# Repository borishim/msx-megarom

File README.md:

# msx-megarom
MSX megarom cartridge pcb (kicad)

There are three jumpers to set:
- P8: put a jumper for 8kB bank, otherwise 16kB
- P7 and P2: bank selection bits (WA and WB). Depends on the mapper type.

For example,
```
                           8kB WA  WB
                     ASC8: YES A11 A12
                    ASC16: NO  A12 0
                 Generic8: YES A13 A15
                Generic16: NO  A15 0
               Konami SCC: YES A13 A15
            Konami no SCC: YES A13 A15
Super Game World 30/64/80: YES A0  A1
            Super Pierrot: NO  A12 0
```
Also take a look https://www.msx.org/wiki/MegaROM_Mappers

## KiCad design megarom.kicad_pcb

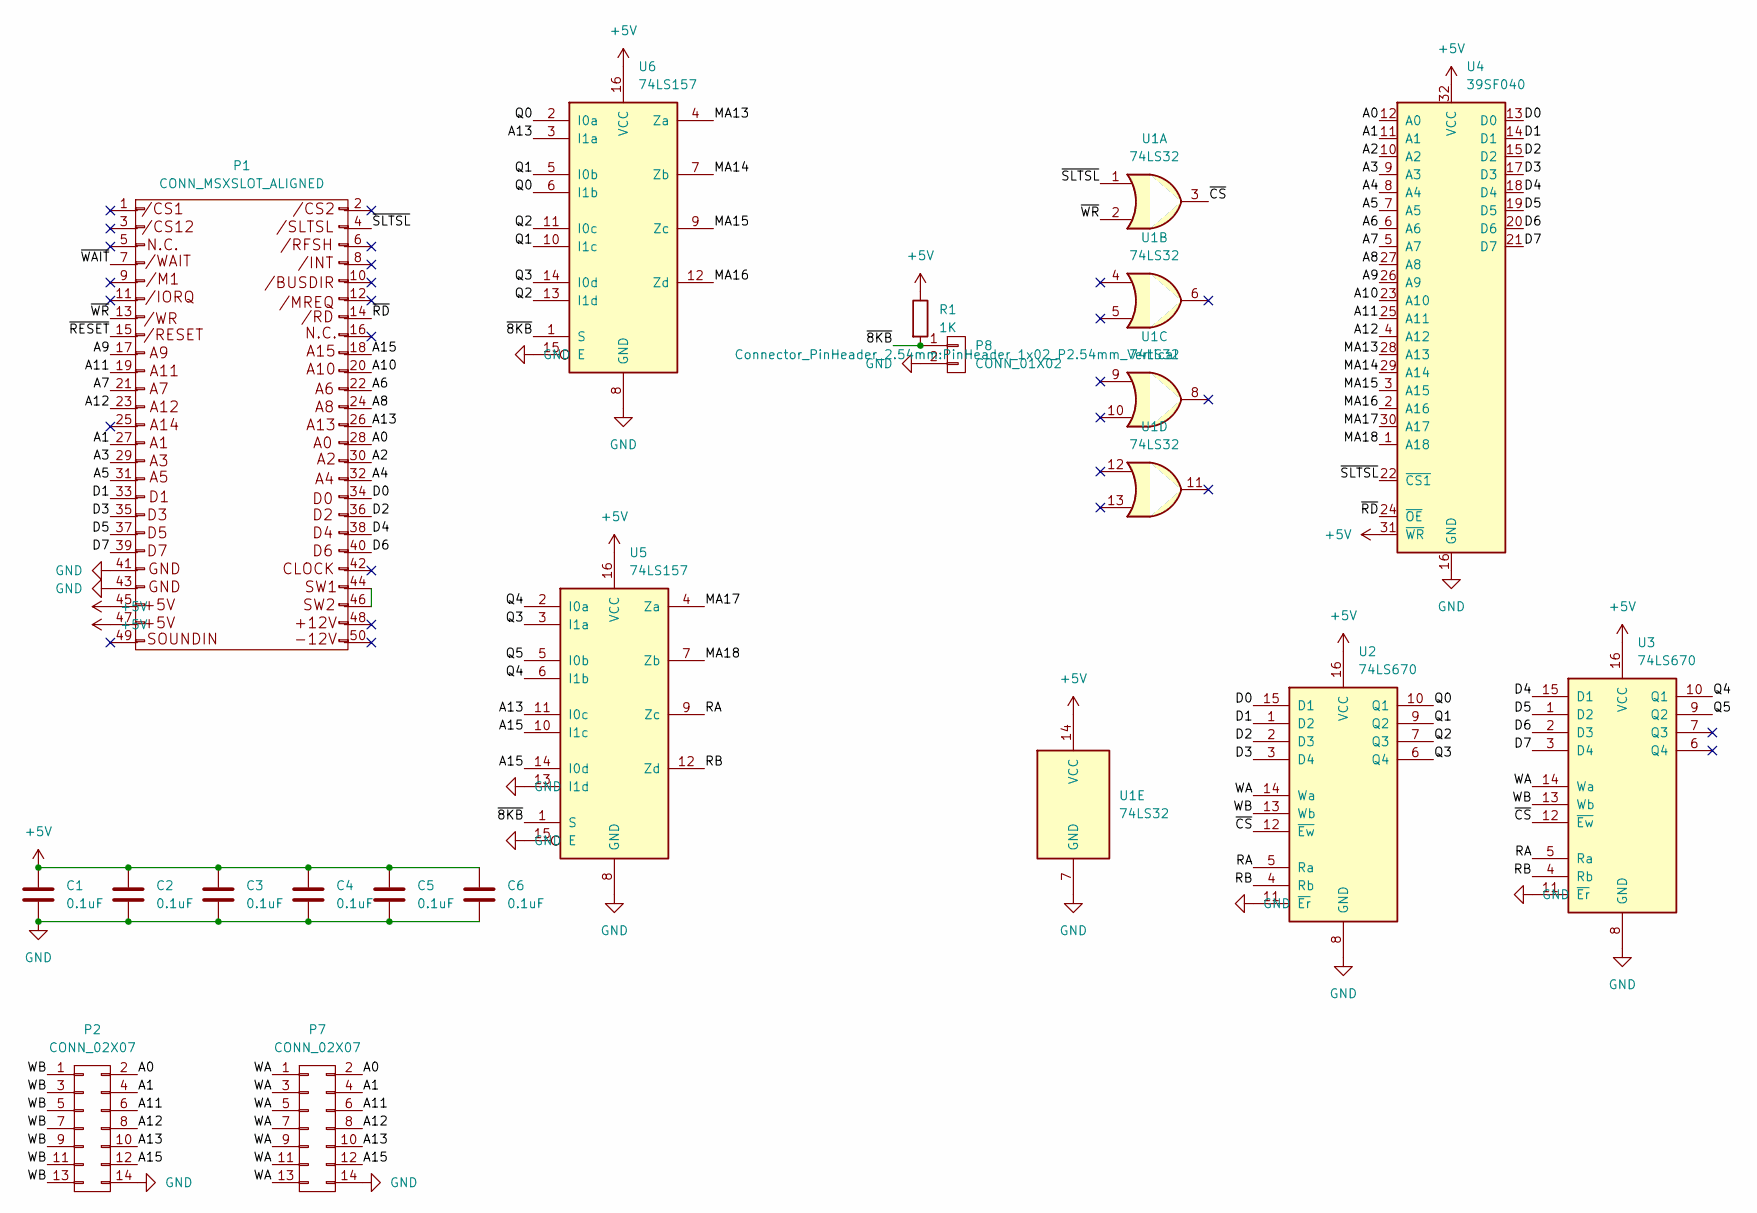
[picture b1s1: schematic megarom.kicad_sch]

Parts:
C1, C2, C3, C4, C5, C6: 0.1uF; C_Disc_D4.3mm_W1.9mm_P5.00mm
P1: CONN_MSXSLOT_ALIGNED; card_edge_connector
P2, P7: CONN_02X07; PinHeader_2x07_P2.54mm_Vertical
P8: CONN_01X02; PinHeader_1x02_P2.54mm_Vertical
R1: 1K; R_Axial_DIN0207_L6.3mm_D2.5mm_P10.16mm_Horizontal
U1: 74LS32; DIP-14_W7.62mm_LongPads
U2, U3: 74LS670; DIP-16_W7.62mm_LongPads
U4: 39SF040; DIP-32_W15.24mm_LongPads
U5, U6: 74LS157; DIP-16_W7.62mm_LongPads

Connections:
+5V: C1.1, C2.1, C3.1, C4.1, C5.1, C6.1, P1.45, P1.47, R1.1, U1.14 (VCC), U2.16 (VCC), U3.16 (VCC), U4.31 (~WR), U4.32 (VCC), U5.16 (VCC), U6.16 (VCC)
/A0: P1.28, P2.2, P7.2, U4.12 (A0)
/A1: P1.27, P2.4, P7.4, U4.11 (A1)
/A2: P1.30, U4.10 (A2)
/A3: P1.29, U4.9 (A3)
/A4: P1.32, U4.8 (A4)
/A5: P1.31, U4.7 (A5)
/A6: P1.22, U4.6 (A6)
/A7: P1.21, U4.5 (A7)
/A8: P1.24, U4.27 (A8)
/A9: P1.17, U4.26 (A9)
/A10: P1.20, U4.23 (A10)
/A11: P1.19, P2.6, P7.6, U4.25 (A11)
/A12: P1.23, P2.8, P7.8, U4.4 (A12)
/A13: P1.26, P2.10, P7.10, U5.11 (I0c), U6.3 (I1a)
/A15: P1.18, P2.12, P7.12, U5.10 (I1c), U5.14 (I0d)
/D0: P1.34, U2.15 (D1), U4.13 (D0)
/D1: P1.33, U2.1 (D2), U4.14 (D1)
/D2: P1.36, U2.2 (D3), U4.15 (D2)
/D3: P1.35, U2.3 (D4), U4.17 (D3)
/D4: P1.38, U3.15 (D1), U4.18 (D4)
/D5: P1.37, U3.1 (D2), U4.19 (D5)
/D6: P1.40, U3.2 (D3), U4.20 (D6)
/D7: P1.39, U3.3 (D4), U4.21 (D7)
/MA13: U4.28 (A13), U6.4 (Za)
/MA14: U4.29 (A14), U6.7 (Zb)
/MA15: U4.3 (A15), U6.9 (Zc)
/MA16: U4.2 (A16), U6.12 (Zd)
/MA17: U4.30 (A17), U5.4 (Za)
/MA18: U4.1 (A18), U5.7 (Zb)
/Q0: U2.10 (Q1), U6.2 (I0a), U6.6 (I1b)
/Q1: U2.9 (Q2), U6.5 (I0b), U6.10 (I1c)
/Q2: U2.7 (Q3), U6.11 (I0c), U6.13 (I1d)
/Q3: U2.6 (Q4), U5.3 (I1a), U6.14 (I0d)
/Q4: U3.10 (Q1), U5.2 (I0a), U5.6 (I1b)
/Q5: U3.9 (Q2), U5.5 (I0b)
/RA: U2.5 (Ra), U3.5 (Ra), U5.9 (Zc)
/RB: U2.4 (Rb), U3.4 (Rb), U5.12 (Zd)
/WA: P7.1, P7.3, P7.5, P7.7, P7.9, P7.11, P7.13, U2.14 (Wa), U3.14 (Wa)
/WB: P2.1, P2.3, P2.5, P2.7, P2.9, P2.11, P2.13, U2.13 (Wb), U3.13 (Wb)
/~8KB: P8.1, R1.2, U5.1 (S), U6.1 (S)
/~CS: U1.3, U2.12 (~Ew), U3.12 (~Ew)
/~RD: P1.14, U4.24 (~OE)
/~RESET: P1.15
/~SLTSL: P1.4, U1.1, U4.22 (~CS1)
/~WAIT: P1.7
/~WR: P1.13, U1.2
GND: C1.2, C2.2, C3.2, C4.2, C5.2, C6.2, P1.41, P1.43, P2.14, P7.14, P8.2, U1.7 (GND), U2.8 (GND), U2.11 (~Er), U3.8 (GND), U3.11 (~Er), U4.16 (GND), U5.8 (GND), U5.13 (I1d), U5.15 (E), U6.8 (GND), U6.15 (E)
unnamed: P1.44, P1.46

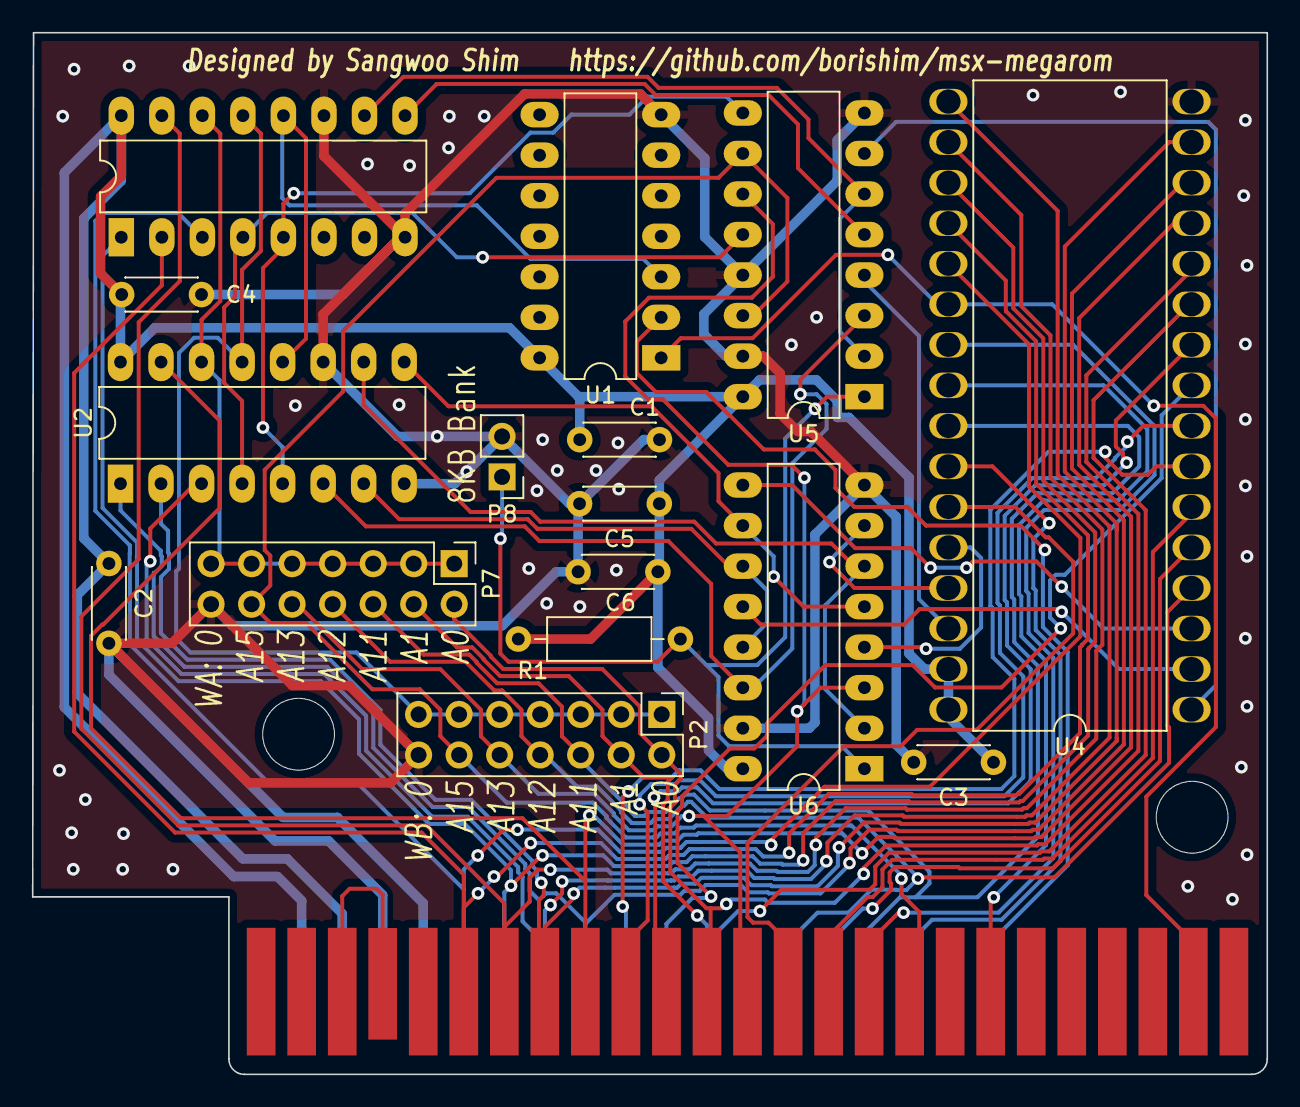
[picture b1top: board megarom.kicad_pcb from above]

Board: 2 copper layers, 77.4 x 65.3 mm, 17 parts (0 on the bottom side), 47 nets.

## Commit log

2022-04-21 Added title, data, revision and comments to the schematics
2022-04-21 Updated schematics pdf
2022-04-21 Added a 3d rendering
